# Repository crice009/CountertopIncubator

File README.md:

# Countertop Incubator
Incubator for making tempeh built from spare 3D printer parts. Specifically designed to meet the discerning needs of a hungry girlfriend, with a background in microbiology..

# Documentation Website
https://crice009.github.io/CountertopIncubator/index.html

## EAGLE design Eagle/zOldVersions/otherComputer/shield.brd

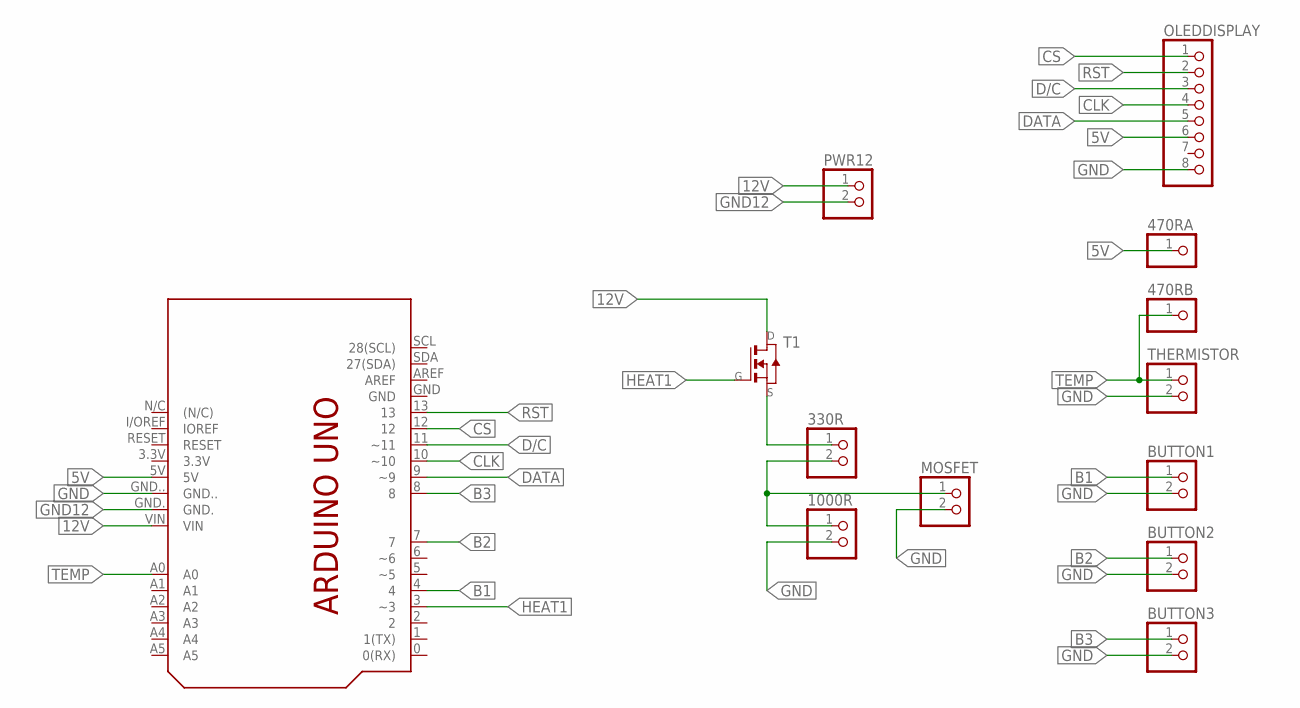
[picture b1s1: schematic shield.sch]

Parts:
330R, 1000R: PINHD-1X2; 1X02
470RA, 470RB: PINHD-1X1; 1X01
BUTTON1, BUTTON2, BUTTON3: PINHD-1X2; 1X02
MOSFET: PINHD-1X2; 1X02
OLEDDISPLAY: PINHD-1X8; 1X08
PCB1: ARDUINO_UNO_UNBOUND
PWR12: PINHD-1X2; 1X02
T1: NMOSFETTO252; TO252
THERMISTOR: PINHD-1X2; 1X02

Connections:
5V: 470RA.1, OLEDDISPLAY.6, PCB1.5V
12V: PCB1.VIN, PWR12.1, T1.3 (D)
B1: BUTTON1.1, PCB1.4
B2: BUTTON2.1, PCB1.7
B3: BUTTON3.1, PCB1.8
CLK: OLEDDISPLAY.4, PCB1.10 (~10)
CS: OLEDDISPLAY.1, PCB1.12
D/C: OLEDDISPLAY.3, PCB1.11 (~11)
DATA: OLEDDISPLAY.5, PCB1.9 (~9)
GND: 1000R.2, BUTTON1.2, BUTTON2.2, BUTTON3.2, MOSFET.2, OLEDDISPLAY.8, PCB1.GND.., THERMISTOR.2
GND12: PCB1.GND., PWR12.2
HEAT1: PCB1.3 (~3), T1.1 (G)
unnamed: 330R.2, 1000R.1, MOSFET.1
unnamed: 330R.1, T1.2 (S)
RST: OLEDDISPLAY.2, PCB1.13
TEMP: 470RB.1, PCB1.A0, THERMISTOR.1

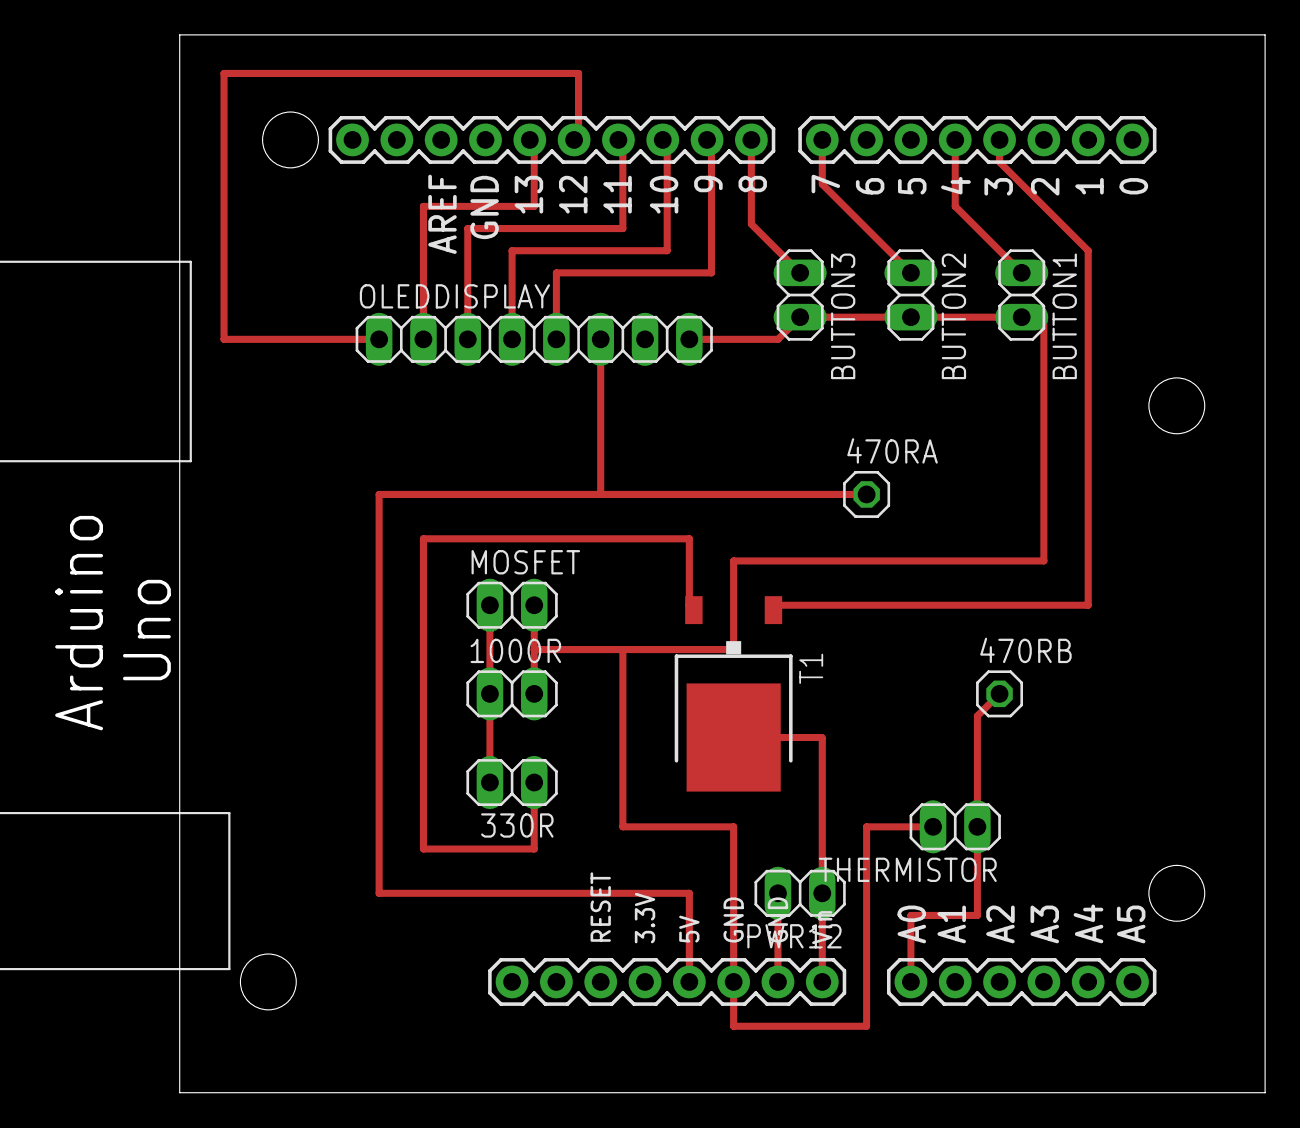
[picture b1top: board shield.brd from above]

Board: 2 copper layers, 70.5 x 60.6 mm, 13 parts (0 on the bottom side), 16 nets.

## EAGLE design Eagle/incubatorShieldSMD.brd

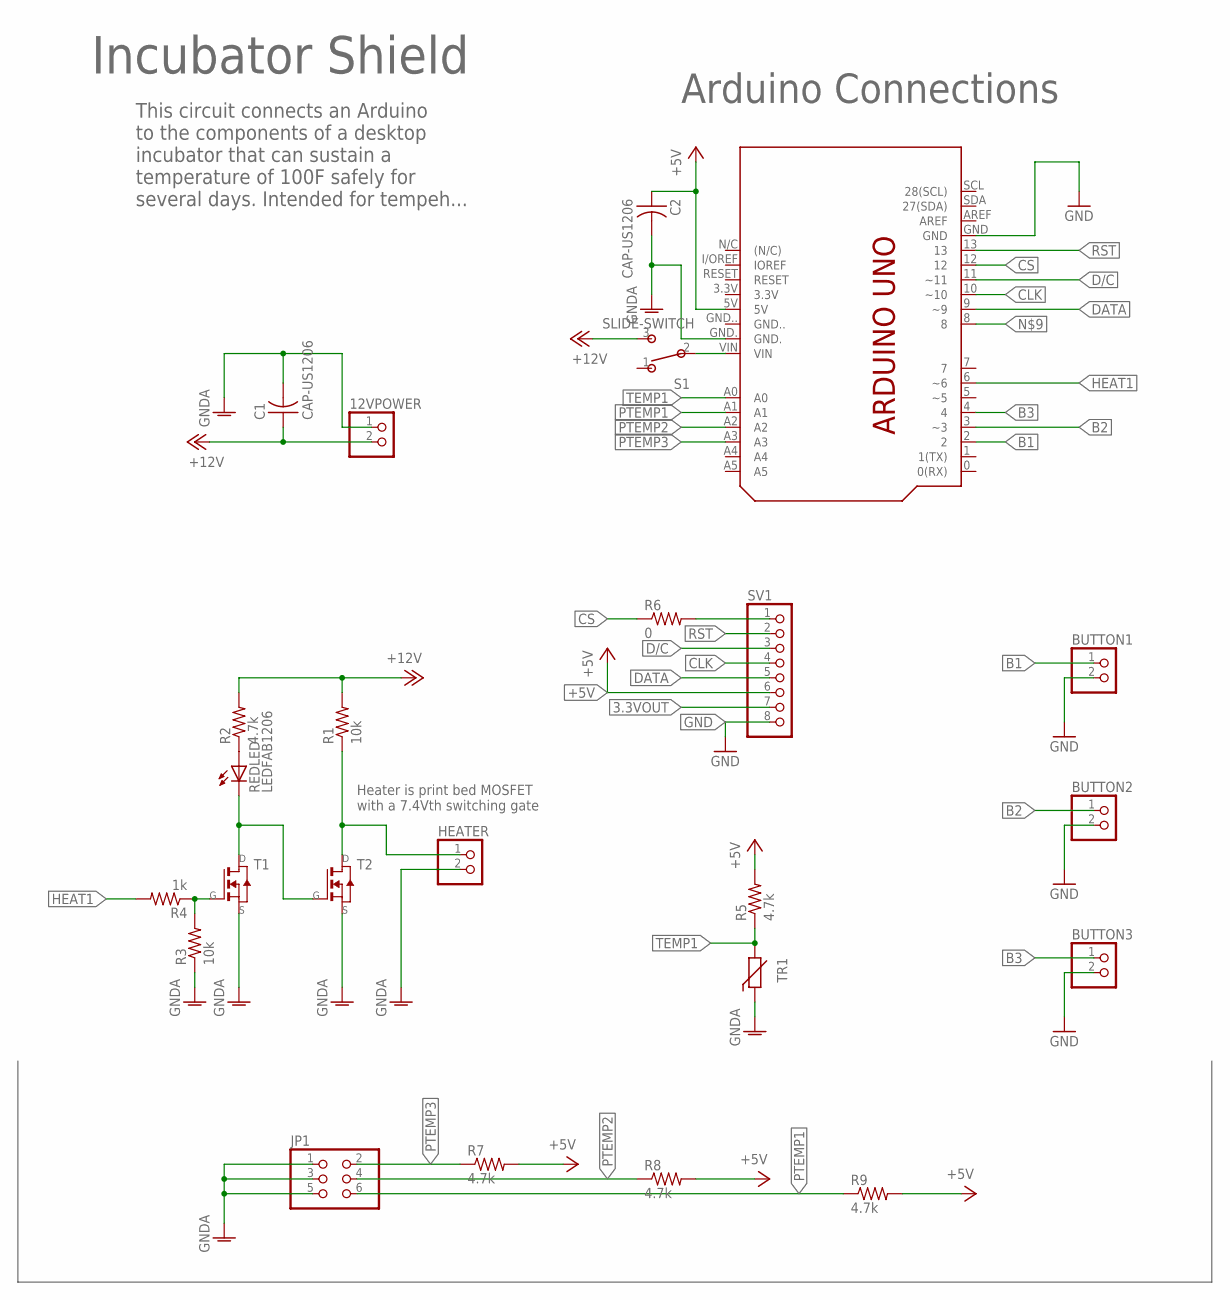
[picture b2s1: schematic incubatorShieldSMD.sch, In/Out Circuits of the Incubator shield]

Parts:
12VPOWER: PINHD-1X2; 1X02
BUTTON1, BUTTON2, BUTTON3: PINHD-1X2; 1X02
C1, C2: CAP-US1206; C1206
HEATER: PINHD-1X2; 1X02
JP1: PINHD-2X3-SMD; 2X03SMD
R1, R3: 10k; R1206FAB
R2, R5, R7, R8, R9: 4.7k; R1206FAB
R4: 1k; R1206FAB
R6: 0; R1206FAB
REDLED: LEDFAB1206; LED1206FAB
S1: SLIDE-SWITCH; AYZ0102AGRLC
SV1: PINHD-1X8; 1X08
T1, T2: NMOSFETSOT23; SOT-23
TR1: THERMISTOR_R-2,5; RS-2,5
U$2: ARDUINO_UNO_UNBOUND

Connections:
3.3VOUT: SV1.7
+5V: C2.1, R5.2, R7.2, R8.2, R9.2, SV1.6, U$2.5V
+12V: 12VPOWER.2, C1.1, R1.2, R2.2, S1.3
B1: BUTTON1.1, U$2.2
B2: BUTTON2.1, U$2.3 (~3)
B3: BUTTON3.1, U$2.4
CLK: SV1.4, U$2.10 (~10)
CS: R6.1, U$2.12
D/C: SV1.3, U$2.11 (~11)
DATA: SV1.5, U$2.9 (~9)
GND: BUTTON1.2, BUTTON2.2, BUTTON3.2, SV1.8, U$2.GND
GNDA: 12VPOWER.1, C1.2, C2.2, HEATER.2, JP1.1, JP1.3, JP1.5, R3.1, T1.2 (S), T2.2 (S), TR1.1, U$2.GND.
HEAT1: R4.2, U$2.6 (~6)
HEATER_LOGIC: HEATER.1, R1.1, T2.1 (D)
unnamed: REDLED.2 (C), T1.1 (D), T2.3 (G)
unnamed: R6.2, SV1.1
unnamed: R3.2, R4.1, T1.3 (G)
unnamed: R2.1, REDLED.1 (A)
unnamed: S1.2, U$2.VIN
PTEMP1: JP1.6, R9.1, U$2.A1
PTEMP2: JP1.4, R8.1, U$2.A2
PTEMP3: JP1.2, R7.1, U$2.A3
RST: SV1.2, U$2.13
TEMP1: R5.1, TR1.2, U$2.A0

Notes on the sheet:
Heater is print bed MOSFET with a 7.4Vth switching gate
Incubator Shield
This circuit connects an Arduino to the components of a desktop incubator that can sustain a temperature of 100F safely for several days. Intended for tempeh...
Arduino Connections

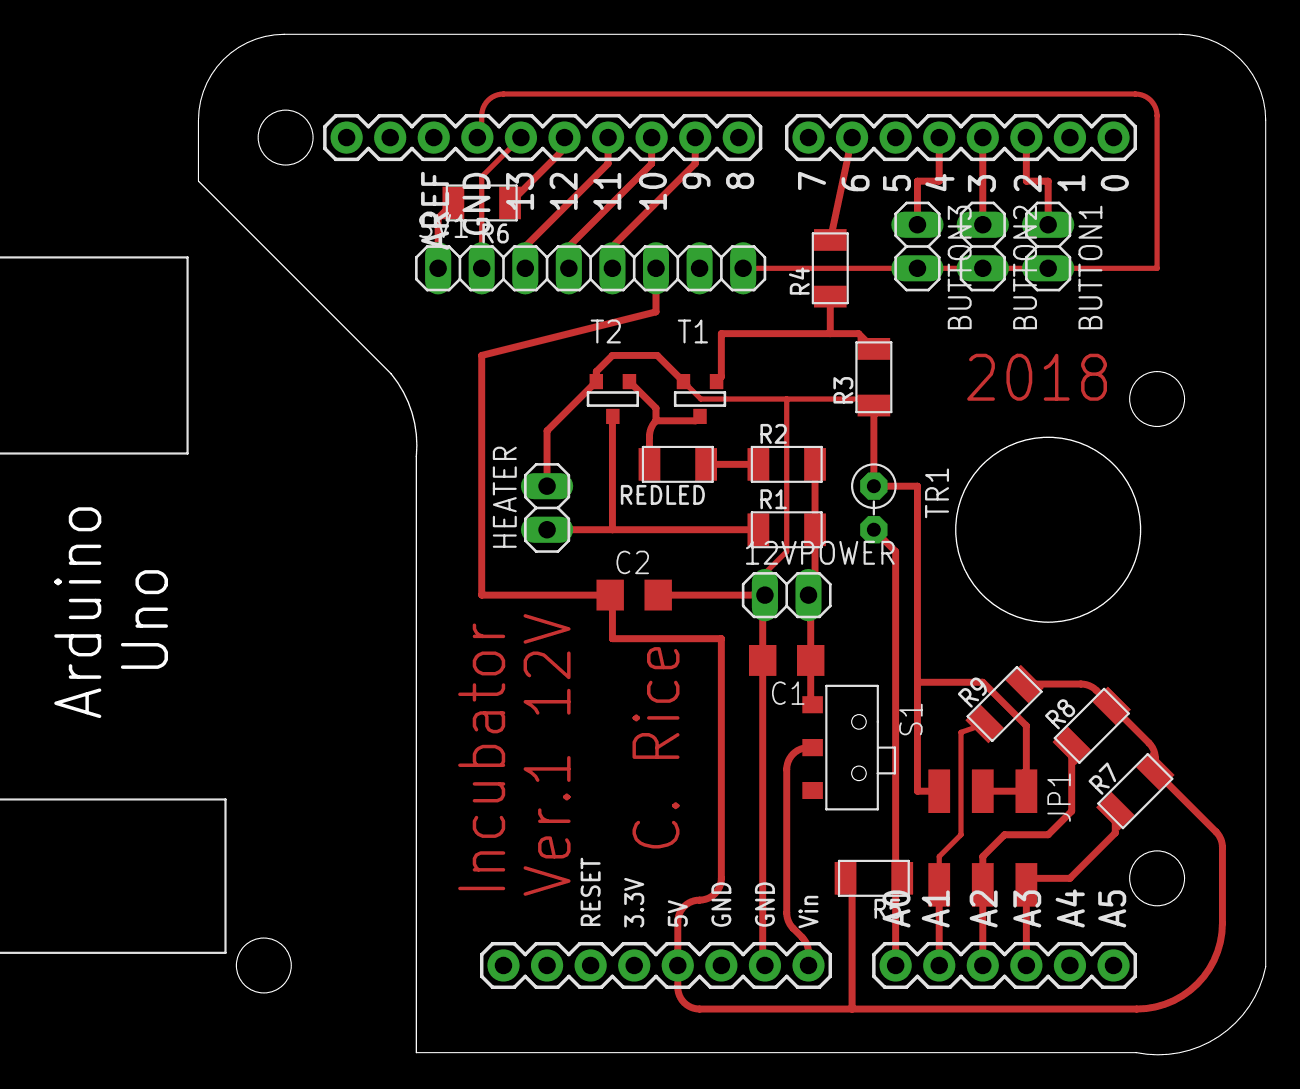
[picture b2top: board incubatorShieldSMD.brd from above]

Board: 2 copper layers, 71.7 x 59.4 mm, 24 parts (0 on the bottom side), 23 nets.

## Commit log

2017-12-29 inital upload
2017-12-29 website changes
2017-12-29 website changes 2
2017-12-29 website changes 3
2017-12-29 website changes 4
2017-12-29 website changes 5
2018-01-02 circuit image
2018-01-03 more subpages
2018-01-03 food
2018-01-03 fermento
2018-01-03 silly
2018-01-03 worklaptop
2018-01-04 marlin work
2018-01-04 configuration.h
2018-01-04 understanding marlin
2018-01-04 Thursday's work
2018-01-05 continuing with temp files...
2018-01-07 finally building a tempTest that is based on what is needed...
2018-01-08 simple working version
2018-01-08 organized arduino
2018-01-09 it works!
2018-01-10 it works!2
2018-01-10 some UI stuff
2018-01-10 3d model file
2018-01-10 UI improvements
2018-01-13 still working on count up timer
2018-01-15 it all works
2018-01-15 timer appearance
2018-01-15 bill of materials
2018-01-15 BOM narrative
2018-01-15 favicon
2018-01-15 fix links
2018-01-15 start time
2018-01-15 file structure
2018-01-15 added firmware page
